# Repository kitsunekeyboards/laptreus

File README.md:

# Laptreus
Home of the Laptreus bluetooth Atreus variant that's designed to fit on top of your laptop keyboard

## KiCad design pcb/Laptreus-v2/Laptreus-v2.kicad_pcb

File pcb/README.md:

# First pcb project

Following along with this:

* https://github.com/ruiqimao/keyboard-pcb-guide

General KiCad:

* http://docs.kicad-pcb.org/stable/en/getting_started_in_kicad.html#kicad-work-flow

KiCad parts:

* https://github.com/tmk/kicad_lib_tmk
* https://github.com/tmk/keyboard_parts.pretty
* https://github.com/egladman/keebs.pretty

Board I want to emulate:

* https://github.com/wolffjj/Atreus_54percent

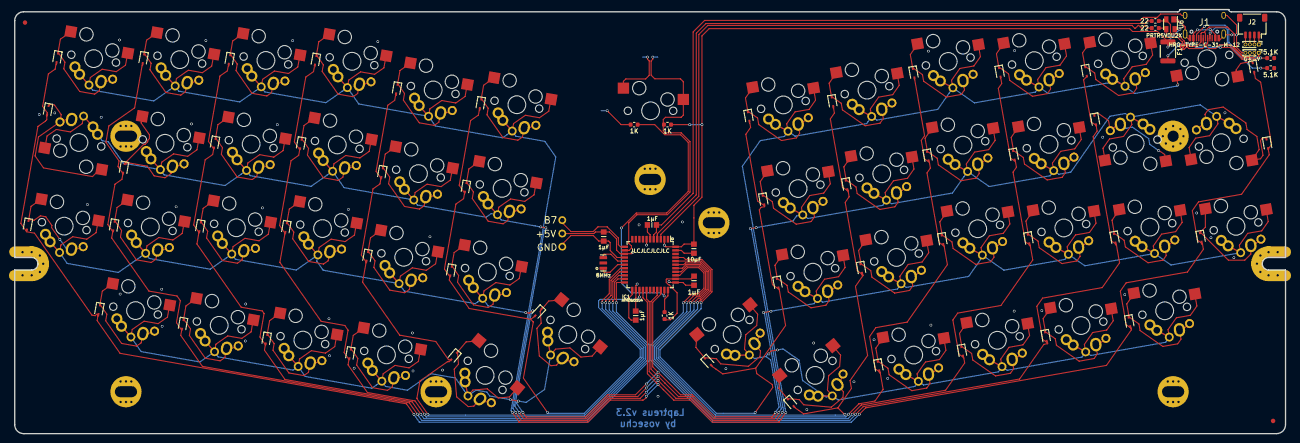
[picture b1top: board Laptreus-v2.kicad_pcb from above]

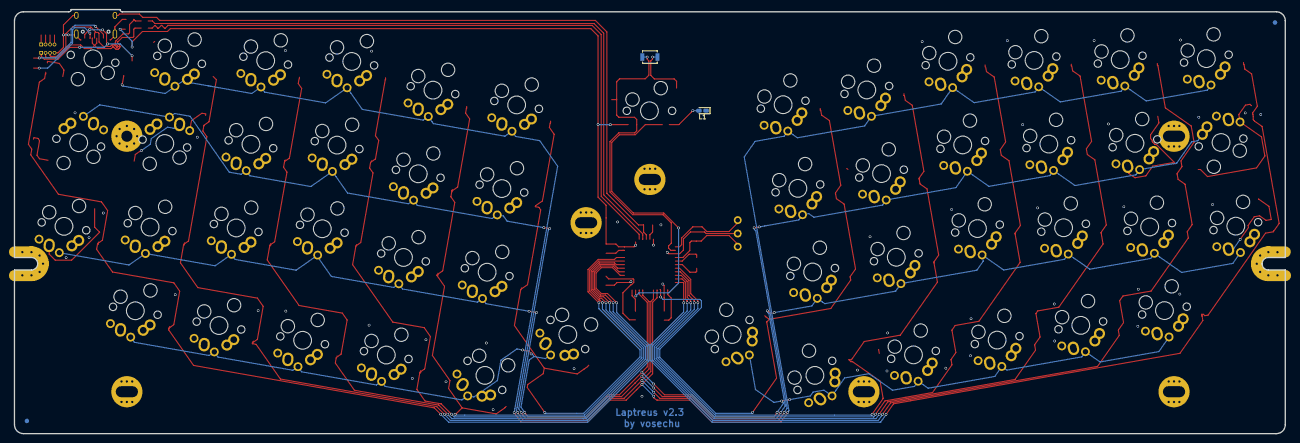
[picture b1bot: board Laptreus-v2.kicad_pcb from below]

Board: 2 copper layers, 285.0 x 95.1 mm, 129 parts (5 on the bottom side), 85 nets.

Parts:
BOARD1: BoardOutline; 60-percent-plus-tofu
C2, C4, C5, C7: 1µF; Capacitor-0805MP
C3: 10µF; Capacitor-0805MP
D1, D2, D3, D4, D5, D6, D7, D8, D9, D10, D11, D12, D13, D14, D15, D16, D17, D18, D19, D20, D21, D22, D23, D24, D25, D26, D27, D28, D29, D30, D31, D32, D33, D34, D35, D36, D37, D38, D39, D40, D41, D42, D43, D44, D45, D46, D47, D48: DIODE; D_SOD-323_With_Adhesive
F1: Polyfuse; Fuse_1812_4532Metric_With_Adhesive
FID1, FID2, FID3, FID4: Fiducial; FIDUCIAL
IC1: ATMEGA32U4; TQFP-44_10x10mm_P0.8mm
J1: HRO-TYPE-C-31-M-12
J2: Conn_01x04; JST_SH_SM04B-SRSS-TB_1x04-1MP_P1.00mm_Horizontal
J3, J4: Conn_01x04_Female; PinHeader_1x04_P1.00mm_Vertical
JP1, JP2, JP3: PINHD-1X1CB; 1X01-CLEANBIG
KittyB: Val**; Kitty
KittyF: Val**; Kitty
L1: YELLOW; LED_0603_1608Metric_Castellated
R1, R10, R13: 1K; R_0603_1608Metric_With_Adhesive
R8, R9: 22; R_0603_1608Metric_With_Adhesive
R11, R12: 5.1K; R_0603_1608Metric_With_Adhesive
SW1: TAB; Kailh_Socket_With_Diode_No_Diode_Trace
SW2: Q; Hybrid_Kailh_MX_Choc_Socket_Through_Hole_With_Diode
SW3: W; Hybrid_Kailh_MX_Choc_Socket_Through_Hole_With_Diode
SW4: E; Hybrid_Kailh_MX_Choc_Socket_Through_Hole_With_Diode
SW5: R; Hybrid_Kailh_MX_Choc_Socket_Through_Hole_With_Diode
SW6: T; Hybrid_Kailh_MX_Choc_Socket_Through_Hole_With_Diode
SW7: Y; Hybrid_Kailh_MX_Choc_Socket_Through_Hole_With_Diode
SW8: U; Hybrid_Kailh_MX_Choc_Socket_Through_Hole_With_Diode
SW9: I; Hybrid_Kailh_MX_Choc_Socket_Through_Hole_With_Diode
SW10: O; Hybrid_Kailh_MX_Choc_Socket_Through_Hole_With_Diode
SW11: P; Hybrid_Kailh_MX_Choc_Socket_Through_Hole_With_Diode
SW12: BKSP; Hybrid_Kailh_MX_Choc_Socket_Through_Hole_With_Diode
SW13: ESC; Hybrid_Kailh_MX_Choc_Socket_Through_Hole_With_Diode
SW14: A; Hybrid_Kailh_MX_Choc_Socket_Through_Hole_With_Diode_No_Diod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
SW15: S; Hybrid_Kailh_MX_Choc_Socket_Through_Hole_With_Diode
SW16: D; Hybrid_Kailh_MX_Choc_Socket_Through_Hole_With_Diode
SW17: F/LOWER; Hybrid_Kailh_MX_Choc_Socket_Through_Hole_With_Diode
SW18: G; Hybrid_Kailh_MX_Choc_Socket_Through_Hole_With_Diode
SW19: H; Hybrid_Kailh_MX_Choc_Socket_Through_Hole_With_Diode
SW20: J/RAISE; Hybrid_Kailh_MX_Choc_Socket_Through_Hole_With_Diode
SW21: K; Hybrid_Kailh_MX_Choc_Socket_Through_Hole_With_Diode
SW22: L; Hybrid_Kailh_MX_Choc_Socket_Through_Hole_With_Diode
SW23: ;; Hybrid_Kailh_MX_Choc_Socket_Through_Hole_With_Diode_No_Diod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
SW24: "; Hybrid_Kailh_MX_Choc_Socket_Through_Hole_With_Diode_No_Diod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
SW25: SHIFT; Hybrid_Kailh_MX_Choc_Socket_Through_Hole_With_Diode_No_Diod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
SW26: Z; Hybrid_Kailh_MX_Choc_Socket_Through_Hole_With_Diode
SW27: X; Hybrid_Kailh_MX_Choc_Socket_Through_Hole_With_Diode
SW28: C; Hybrid_Kailh_MX_Choc_Socket_Through_Hole_With_Diode
SW29: V; Hybrid_Kailh_MX_Choc_Socket_Through_Hole_With_Diode
SW30: B; Hybrid_Kailh_MX_Choc_Socket_Through_Hole_With_Diode
SW31: N; Hybrid_Kailh_MX_Choc_Socket_Through_Hole_With_Diode
SW32: M; Hybrid_Kailh_MX_Choc_Socket_Through_Hole_With_Diode
SW33: ,; Hybrid_Kailh_MX_Choc_Socket_Through_Hole_With_Diode
SW34: .; Hybrid_Kailh_MX_Choc_Socket_Through_Hole_With_Diode
SW35: /; Hybrid_Kailh_MX_Choc_Socket_Through_Hole_With_Diode
SW36: ENTER; Hybrid_Kailh_MX_Choc_Socket_Through_Hole_With_Diode_No_Diod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
SW37: HYPER; Hybrid_Kailh_MX_Choc_Socket_Through_Hole_With_Diode
SW38: CTRL/GRV; Hybrid_Kailh_MX_Choc_Socket_Through_Hole_With_Diode
SW39: ALT/TAB; Hybrid_Kailh_MX_Choc_Socket_Through_Hole_With_Diode
SW40: CMD; Hybrid_Kailh_MX_Choc_Socket_Through_Hole_With_Diode
SW41: SHIFT; Hybrid_Kailh_MX_Choc_Socket_Through_Hole_With_Diode
SW42: BKSP/LIFT; Hybrid_Kailh_MX_Choc_Socket_Through_Hole_With_Diode
SW43: ENTER/LIFT; Hybrid_Kailh_MX_Choc_Socket_Through_Hole_With_Diode
SW44: SPACE; Hybrid_Kailh_MX_Choc_Socket_Through_Hole_With_Diode
SW45: LEFT; Hybrid_Kailh_MX_Choc_Socket_Through_Hole_With_Diode
SW46: DOWN; Hybrid_Kailh_MX_Choc_Socket_Through_Hole_With_Diode
SW47: UP; Hybrid_Kailh_MX_Choc_Socket_Through_Hole_With_Diode
SW48: RIGHT; Hybrid_Kailh_MX_Choc_Socket_Through_Hole_With_Diode
SW_RESET1: SWITCH_PUSH; SW_SPST_B3U-1000P
SW_RESET2: SWITCH_PUSH; Kailh_Socket_With_Diode_No_Diode_Trace
U6: PRTR5V0U2X; SOT-143_With_Adhesive
Y1: 8MHz; RESONATOR-SMD

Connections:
+5V: C2.1, C3.1, C4.1, C5.1, F1.1, IC1.2, IC1.7, IC1.14, IC1.24, IC1.34, IC1.44, JP3.1, R1.2, U6.4
+5VRAW: F1.2, J1.2, J1.11, J3.1
/B7-LED-STRIP: IC1.12, JP1.1
/C7-13: IC1.32, R13.2
/COL0: D12.2, D24.2, D36.2, D48.2, IC1.22
/COL1: D11.2, D23.2, D35.2, D47.2, IC1.21
/COL2: D10.2, D22.2, D34.2, D46.2, IC1.20
/COL3: D9.2, D21.2, D33.2, D45.2, IC1.19
/COL4: D8.2, D20.2, D32.2, D44.2, IC1.18
/COL5: D7.2, D19.2, D31.2, D43.2, IC1.25
/COL6: D6.2, D18.2, D30.2, D42.2, IC1.41
/COL7: D5.2, D17.2, D29.2, D41.2, IC1.40
/COL8: D4.2, D16.2, D28.2, D40.2, IC1.39
/COL9: D3.2, D15.2, D27.2, D39.2, IC1.38
/COL10: D2.2, D14.2, D26.2, D38.2, IC1.37
/COL11: D1.2, D13.2, D25.2, D37.2, IC1.36
/DR+: IC1.4, R8.1
/DR-: IC1.3, R9.2
/HWB: IC1.33, R10.2
/RESET: IC1.13, R1.1, SW_RESET1.1, SW_RESET2.1
/ROW0: IC1.26, SW1.1, SW2.1, SW3.1, SW4.1, SW5.1, SW6.1, SW7.1, SW8.1, SW9.1, SW10.1, SW11.1, SW12.1
/ROW1: IC1.27, SW13.1, SW14.1, SW15.1, SW16.1, SW17.1, SW18.1, SW19.1, SW20.1, SW21.1, SW22.1, SW23.1, SW24.1
/ROW2: IC1.30, SW25.1, SW26.1, SW27.1, SW28.1, SW29.1, SW30.1, SW31.1, SW32.1, SW33.1, SW34.1, SW35.1, SW36.1
/ROW3: IC1.31, SW37.1, SW38.1, SW39.1, SW40.1, SW41.1, SW42.1, SW43.1, SW44.1, SW45.1, SW46.1, SW47.1, SW48.1
/UCAP: C7.1, IC1.6
/XTAL1: IC1.17, Y1.1
/XTAL2: IC1.16, Y1.3
D+: J1.6, J1.8, J3.3, R8.2, U6.2
D-: J1.5, J1.7, J3.2, R9.1, U6.3
GND: BOARD1.1, C2.2, C3.2, C4.2, C5.2, C7.2, IC1.5, IC1.15, IC1.23, IC1.35, IC1.43, J1.1, J1.12, J1.13, J3.4, JP2.1, L1.1, R10.1, R11.2, R12.1, SW_RESET1.2, SW_RESET2.2, U6.1, Y1.2
unnamed: D1.1, SW1.2
unnamed: D2.1, SW2.2
unnamed: D3.1, SW3.2
unnamed: D4.1, SW4.2
unnamed: D5.1, SW5.2
unnamed: D6.1, SW6.2
unnamed: D7.1, SW7.2
unnamed: D8.1, SW8.2
unnamed: D9.1, SW9.2
unnamed: D10.1, SW10.2
unnamed: D11.1, SW11.2
unnamed: D12.1, SW12.2
unnamed: D13.1, SW13.2
unnamed: D14.1, SW14.2
unnamed: D15.1, SW15.2
unnamed: D16.1, SW16.2
unnamed: D17.1, SW17.2
unnamed: D18.1, SW18.2
unnamed: D19.1, SW19.2
unnamed: D20.1, SW20.2
unnamed: D21.1, SW21.2
unnamed: D22.1, SW22.2
unnamed: D23.1, SW23.2
unnamed: D24.1, SW24.2
unnamed: D25.1, SW25.2
unnamed: D26.1, SW26.2
unnamed: D27.1, SW27.2
unnamed: D28.1, SW28.2
unnamed: D29.1, SW29.2
unnamed: D30.1, SW30.2
unnamed: D31.1, SW31.2
unnamed: D32.1, SW32.2
unnamed: D33.1, SW33.2
unnamed: D34.1, SW34.2
unnamed: D35.1, SW35.2
unnamed: D36.1, SW36.2
unnamed: D37.1, SW37.2
unnamed: D38.1, SW38.2
unnamed: D39.1, SW39.2
unnamed: D40.1, SW40.2
unnamed: D41.1, SW41.2
unnamed: D42.1, SW42.2
unnamed: D43.1, SW43.2
unnamed: D44.1, SW44.2
unnamed: D45.1, SW45.2
unnamed: D46.1, SW46.2
unnamed: D47.1, SW47.2
unnamed: D48.1, SW48.2
unnamed: J1.4, R12.2
unnamed: J1.10, R11.1
unnamed: J2.1, J4.1
unnamed: J2.2, J4.2
unnamed: J2.3, J4.3
unnamed: J2.4, J4.4
unnamed: L1.2, R13.1

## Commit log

2019-02-04 Adding switch fit tester files
2019-07-12 Adding first attempts at laptreus v2
2019-07-14 switches aligned, leds circled
2019-07-15 Starting work on the atmega layout
2019-08-25 prep for printing v2.1 of the laptre
2019-09-07 v2.2
2019-11-16 v2.3 of shapeshifter 4060, also plate
2019-12-08 Update switch holes for Laserboost
2019-12-23 Not sure
2020-02-05 File renames to accommodate windows
2020-02-05 Update to remove jst-sh connector
2020-02-05 move more files for windows
2020-02-16 Remove reference docs
2020-02-16 remove pcb files from megarepo
